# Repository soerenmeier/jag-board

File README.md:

# Jag Board

Jag board is an attempt to make a pcb which can be used to control
different kinds of rc vehicles. At first the focus will be on rc cars,
which can be controlled via a web interface and a webcam.

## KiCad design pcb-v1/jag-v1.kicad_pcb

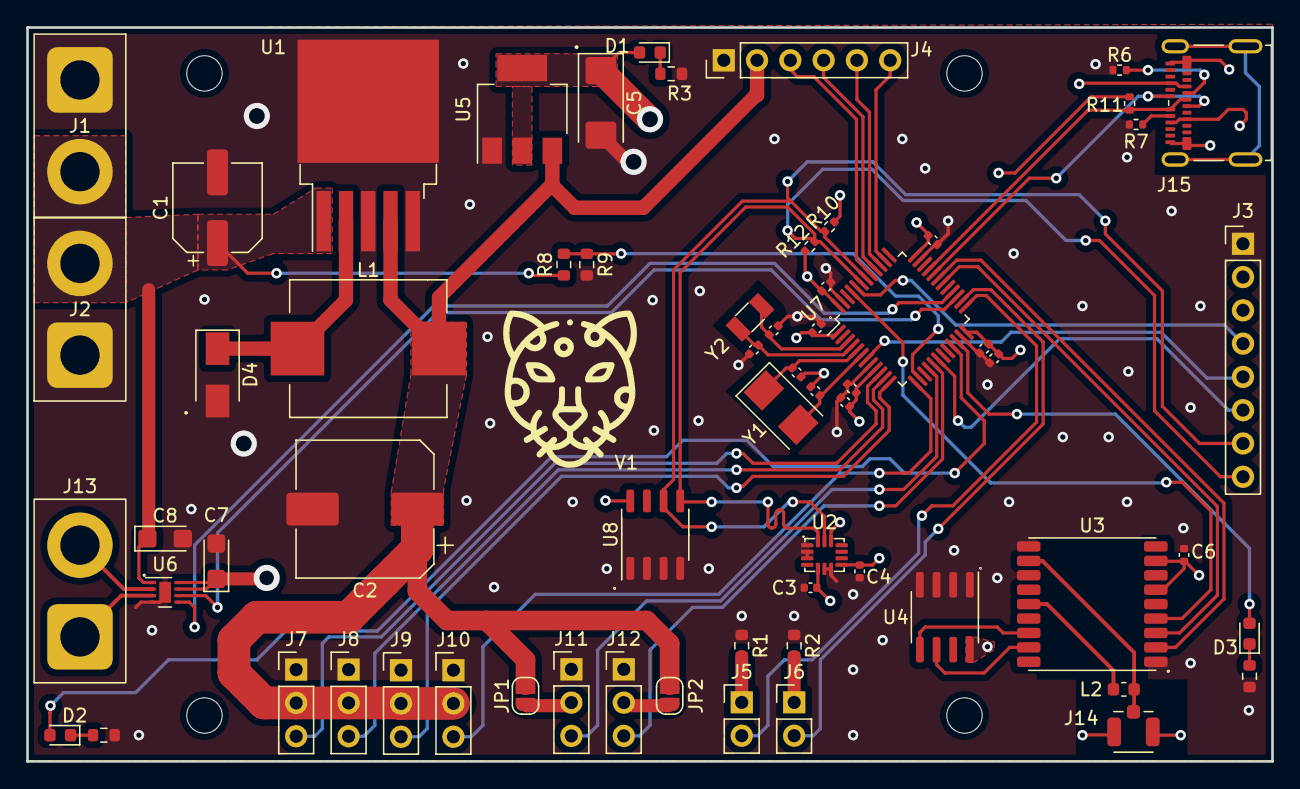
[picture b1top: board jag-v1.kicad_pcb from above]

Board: 4 copper layers, 95.0 x 56.0 mm, 68 parts (0 on the bottom side), 51 nets.

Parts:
C1: 100uF; CP_Elec_6.3x5.8
C2: 220uF; CP_Elec_10x10
C3, C4, C9, C11, C15, C18: 100nF; C_0402_1005Metric
C5: 22uF (tantu); CP_EIA-6032-28_Kemet-C
C6: 10uF; C_0402_1005Metric
C7, C8: 0.1uF; CP_EIA-3216-10_Kemet-I
C10: 10nF; C_0402_1005Metric
C12: 1uF; C_0402_1005Metric
C13, C14: 30pF; C_0402_1005Metric
C16, C17: 18pF; C_0402_1005Metric
C19: 4.7uF; C_0402_1005Metric
D1: Power LED; LED_0603_1608Metric
D2: LED1; LED_0603_1608Metric
D3: LED2; LED_0603_1608Metric
D4: Schottky; D_SMA
H1, H2, H3, H4: MountingHole; MountingHole_2.7mm_M2.5
J1: Battery; Batt Connector
J2: Battery Con 2; Batt Connector
J3: Debug; PinHeader_1x08_P2.54mm_Vertical
J4: Raspberry Pie; PinHeader_1x06_P2.54mm_Vertical
J5: Ext LED1; PinHeader_1x02_P2.54mm_Vertical
J6: Ext LED2; PinHeader_1x02_P2.54mm_Vertical
J7: Servo 1; PinHeader_1x03_P2.54mm_Vertical
J8: Servo 2; PinHeader_1x03_P2.54mm_Vertical
J9: Servo 3; PinHeader_1x03_P2.54mm_Vertical
J10: Servo 4; PinHeader_1x03_P2.54mm_Vertical
J11: Esc 1; PinHeader_1x03_P2.54mm_Vertical
J12: Esc 2; PinHeader_1x03_P2.54mm_Vertical
J13: DC Motor 1; Batt Connector
J14: GPS Antenna; C434807
J15: USB C; USB_C_MOLEX
JP1, JP2: Servo 3 Jumper; SolderJumper-2_P1.3mm_Open_RoundedPad1.0x1.5mm
L1: 68uH; YSPI1050
L2: 47nH; L_0603_1608Metric
R1, R2, R3, R4, R5: 300; R_0603_1608Metric
R6, R7: 5.1K; R_0402_1005Metric
R8: 33K; R_0603_1608Metric
R9: 7.5K; R_0603_1608Metric
R10, R12: 33K; R_0402_1005Metric
R11: 1.5k; R_0402_1005Metric
U1: LM2576HVS-5; TO-263-5_TabPin3
U2: LSM6DSR
U3: ATGM336H-5N
U4: EEPROM 64K; SOIC-8_3.9x4.9mm_P1.27mm
U5: AMS1117-3.3; SOT-223-3_TabPin2
U6: DRV8837C; WSON-8-1EP_2x2mm_P0.5mm_EP0.9x1.6mm
U7: STM32F302C8Tx; LQFP-48_7x7mm_P0.5mm
U8: AT24C256C; SO-8_3.9x4.9mm_P1.27mm
Y1: Crystal @ 8MHz 20pF; Crystal_SMD_5032-2Pin_5.0x3.2mm
Y2: Crystal @ 32.768kHz 12.5pF; Crystal_SMD_3215-2Pin_3.2x1.5mm

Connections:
1PPS: U3.4 (1PPS), U7.45 (PB8)
+3V3: C3.2, C4.1, C5.1, C6.2, C7.1, C9.2, C10.2, C11.2, C12.2, C15.2, C18.2, C19.2, D1.2 (A), J3.3, R10.2, R11.2, R12.2, U2.5 (VDDIO), U2.8 (VDD), U2.12 (CS), U3.6 (VBAT), U3.8 (VCC), U4.8 (VCC), U5.2 (VO), U6.7 (~SLEEP), U6.8 (VCC), U7.1 (VBAT), U7.9 (VDDA), U7.24 (VDD), U7.36 (VDD), U7.48 (VDD), U8.8 (VCC)
+5V: C2.1, J3.2, J4.2, J7.2, J8.2, J9.2, J10.2, J15.A4 (VBUS), J15.A9 (VBUS), J15.B4 (VBUS), J15.B9 (VBUS), JP1.2 (B), JP2.2 (B), L1.2, U1.4 (FB), U5.3 (VI)
+BATT: C1.1, C8.1, J1.2, J2.2, R8.1, U1.1 (VIN), U6.1 (VM)
ADC1_BAT: R8.2, R9.1, U7.14 (PA4)
BOOT: J3.4, U7.44 (BOOT0)
DC_MOTOR+: J13.2, U6.2 (OUT1)
DC_MOTOR-: J13.1, U6.3 (OUT2)
EEPROM_SCL: U3.17 (SCL), U4.6 (SCL)
EEPROM_SDA: U3.16 (SDA), U4.5 (SDA)
EXT_LED1: J5.2, U7.25 (PB12)
EXT_LED2: J6.2, U7.26 (PB13)
GND: C1.2, C2.2, C3.1, C4.2, C5.2, C6.1, C7.2, C8.2, C9.1, C10.1, C11.1, C12.1, C13.2, C14.1, C15.1, C16.2, C17.1, C18.1, C19.1, D4.2 (A), J1.1, J2.1, J3.1, J4.1, J7.1, J8.1, J9.1, J10.1, J11.1, J12.1, J14.1, J15.A1 (GND), J15.A12 (GND), J15.B1 (GND), J15.B12 (GND), R1.1, R2.1, R3.2, R4.2, R5.2, R6.2, R7.2, R9.2, U1.3 (GND), U1.5 (~ON/OFF), U2.1 (SDO/SA0), U2.2 (SDx), U2.3 (SCx), U2.6 (GND), U2.7 (GND), U3.1 (GND), U3.10 (GND), U3.12 (GND), U4.1 (E0), U4.2 (E1), U4.3 (E2), U4.4 (VSS), U5.1 (GND), U6.4 (GND), U6.9 (GND), U7.8 (VSSA), U7.23 (VSS), U7.35 (VSS), U7.47 (VSS), U8.1 (A0), U8.2 (A1), U8.3 (A2), U8.4 (GND)
GPIO_PB0: J3.6, U7.18 (PB0)
GPS_ANTENNA: J14.2, L2.2, U3.11 (RF_IN)
I2C1_SCL: J3.7, R10.1, U2.13 (SCL), U7.42 (PB6), U8.6 (SCL)
I2C1_SDA: J3.8, R12.1, U2.14 (SDA), U7.43 (PB7), U8.5 (SDA)
LED1: D2.2 (A), U7.21 (PB10)
LED2: D3.2 (A), U7.22 (PB11)
unnamed: D1.1 (K), R3.1
unnamed: D2.1 (K), R4.1
unnamed: D3.1 (K), R5.1
unnamed: D4.1 (K), L1.1, U1.2 (OUT)
unnamed: J5.1, R1.2
unnamed: J6.1, R2.2
unnamed: J11.2, JP1.1 (A)
unnamed: J12.2, JP2.1 (A)
unnamed: J15.A5 (CC1), R7.1
unnamed: J15.B5 (CC2), R6.1
unnamed: L2.1, U3.14 (VCC_RF)
OSC32_IN: C16.1, U7.3 (PC14), Y2.2
OSC32_OUT: C17.2, U7.4 (PC15), Y2.1
OSC_IN: C13.1, U7.5 (PF0), Y1.1
OSC_OUT: C14.2, U7.6 (PF1), Y1.2
RESET: J3.5, U7.7 (NRST)
SPI3_MISO: J4.4, U7.40 (PB4)
SPI3_MOSI: J4.3, U7.41 (PB5)
SPI3_NSS: J4.6, U7.38 (PA15)
SPI3_SCK: J4.5, U7.39 (PB3)
TIM2_PWM1: J7.3, U7.10 (PA0)
TIM2_PWM2: J8.3, U7.11 (PA1)
TIM2_PWM3: J9.3, U7.12 (PA2)
TIM2_PWM4: J10.3, U7.13 (PA3)
TIM15_PWM1: U6.6 (IN1), U7.27 (PB14)
TIM15_PWM2: U6.5 (IN2), U7.28 (PB15)
TIM16_PWM1: J11.3, U7.16 (PA6)
TIM17_PWM1: J12.3, U7.17 (PA7)
USART1_RX: U3.2 (TXD), U7.31 (PA10)
USART1_TX: U3.3 (RXD), U7.30 (PA9)
USB_DM: J15.A7 (D-), J15.B7 (D-), U7.32 (PA11)
USB_DP: J15.A6 (D+), J15.B6 (D+), R11.1, U7.33 (PA12)

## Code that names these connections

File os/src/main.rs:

#![no_std]
#![no_main]

use panic_halt as _;

use cortex_m_rt::entry;
use hal::delay::Delay;
use hal::pac::{CorePeripherals, Peripherals};
use hal::prelude::*;

#[entry]
fn main() -> ! {
	// device core peripherals
	let dcp = CorePeripherals::take().unwrap();
	// device peripherals
	let dp = Peripherals::take().unwrap();

	let mut flash = dp.FLASH.constrain();

	// setup clocks
	let mut rcc = dp.RCC.constrain();
	let clocks = rcc.cfgr.use_hse(8.MHz()).freeze(&mut flash.acr);

	let mut delay = Delay::new(dcp.SYST, clocks);

	let mut gpiob = dp.GPIOB.split(&mut rcc.ahb);

	// PB10
	let mut led1 = gpiob
		.pb10
		.into_push_pull_output(&mut gpiob.moder, &mut gpiob.otyper);
	let mut led2 = gpiob
		.pb11
		.into_push_pull_output(&mut gpiob.moder, &mut gpiob.otyper);

	loop {
		led1.set_low();
		delay.delay_ms(1000u16);
		led1.set_high();

		led2.set_low();
		delay.delay_ms(1000u16);
		led2.set_high();
	}
}

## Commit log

2024-06-21 cargo fmt
